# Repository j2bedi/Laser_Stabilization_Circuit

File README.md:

# Laser stabilization circuit repo 

Kicad 9.0 project files located in repo 

production files(gerber and drill) located within releases

Kindly use kicad 9.0 :-)

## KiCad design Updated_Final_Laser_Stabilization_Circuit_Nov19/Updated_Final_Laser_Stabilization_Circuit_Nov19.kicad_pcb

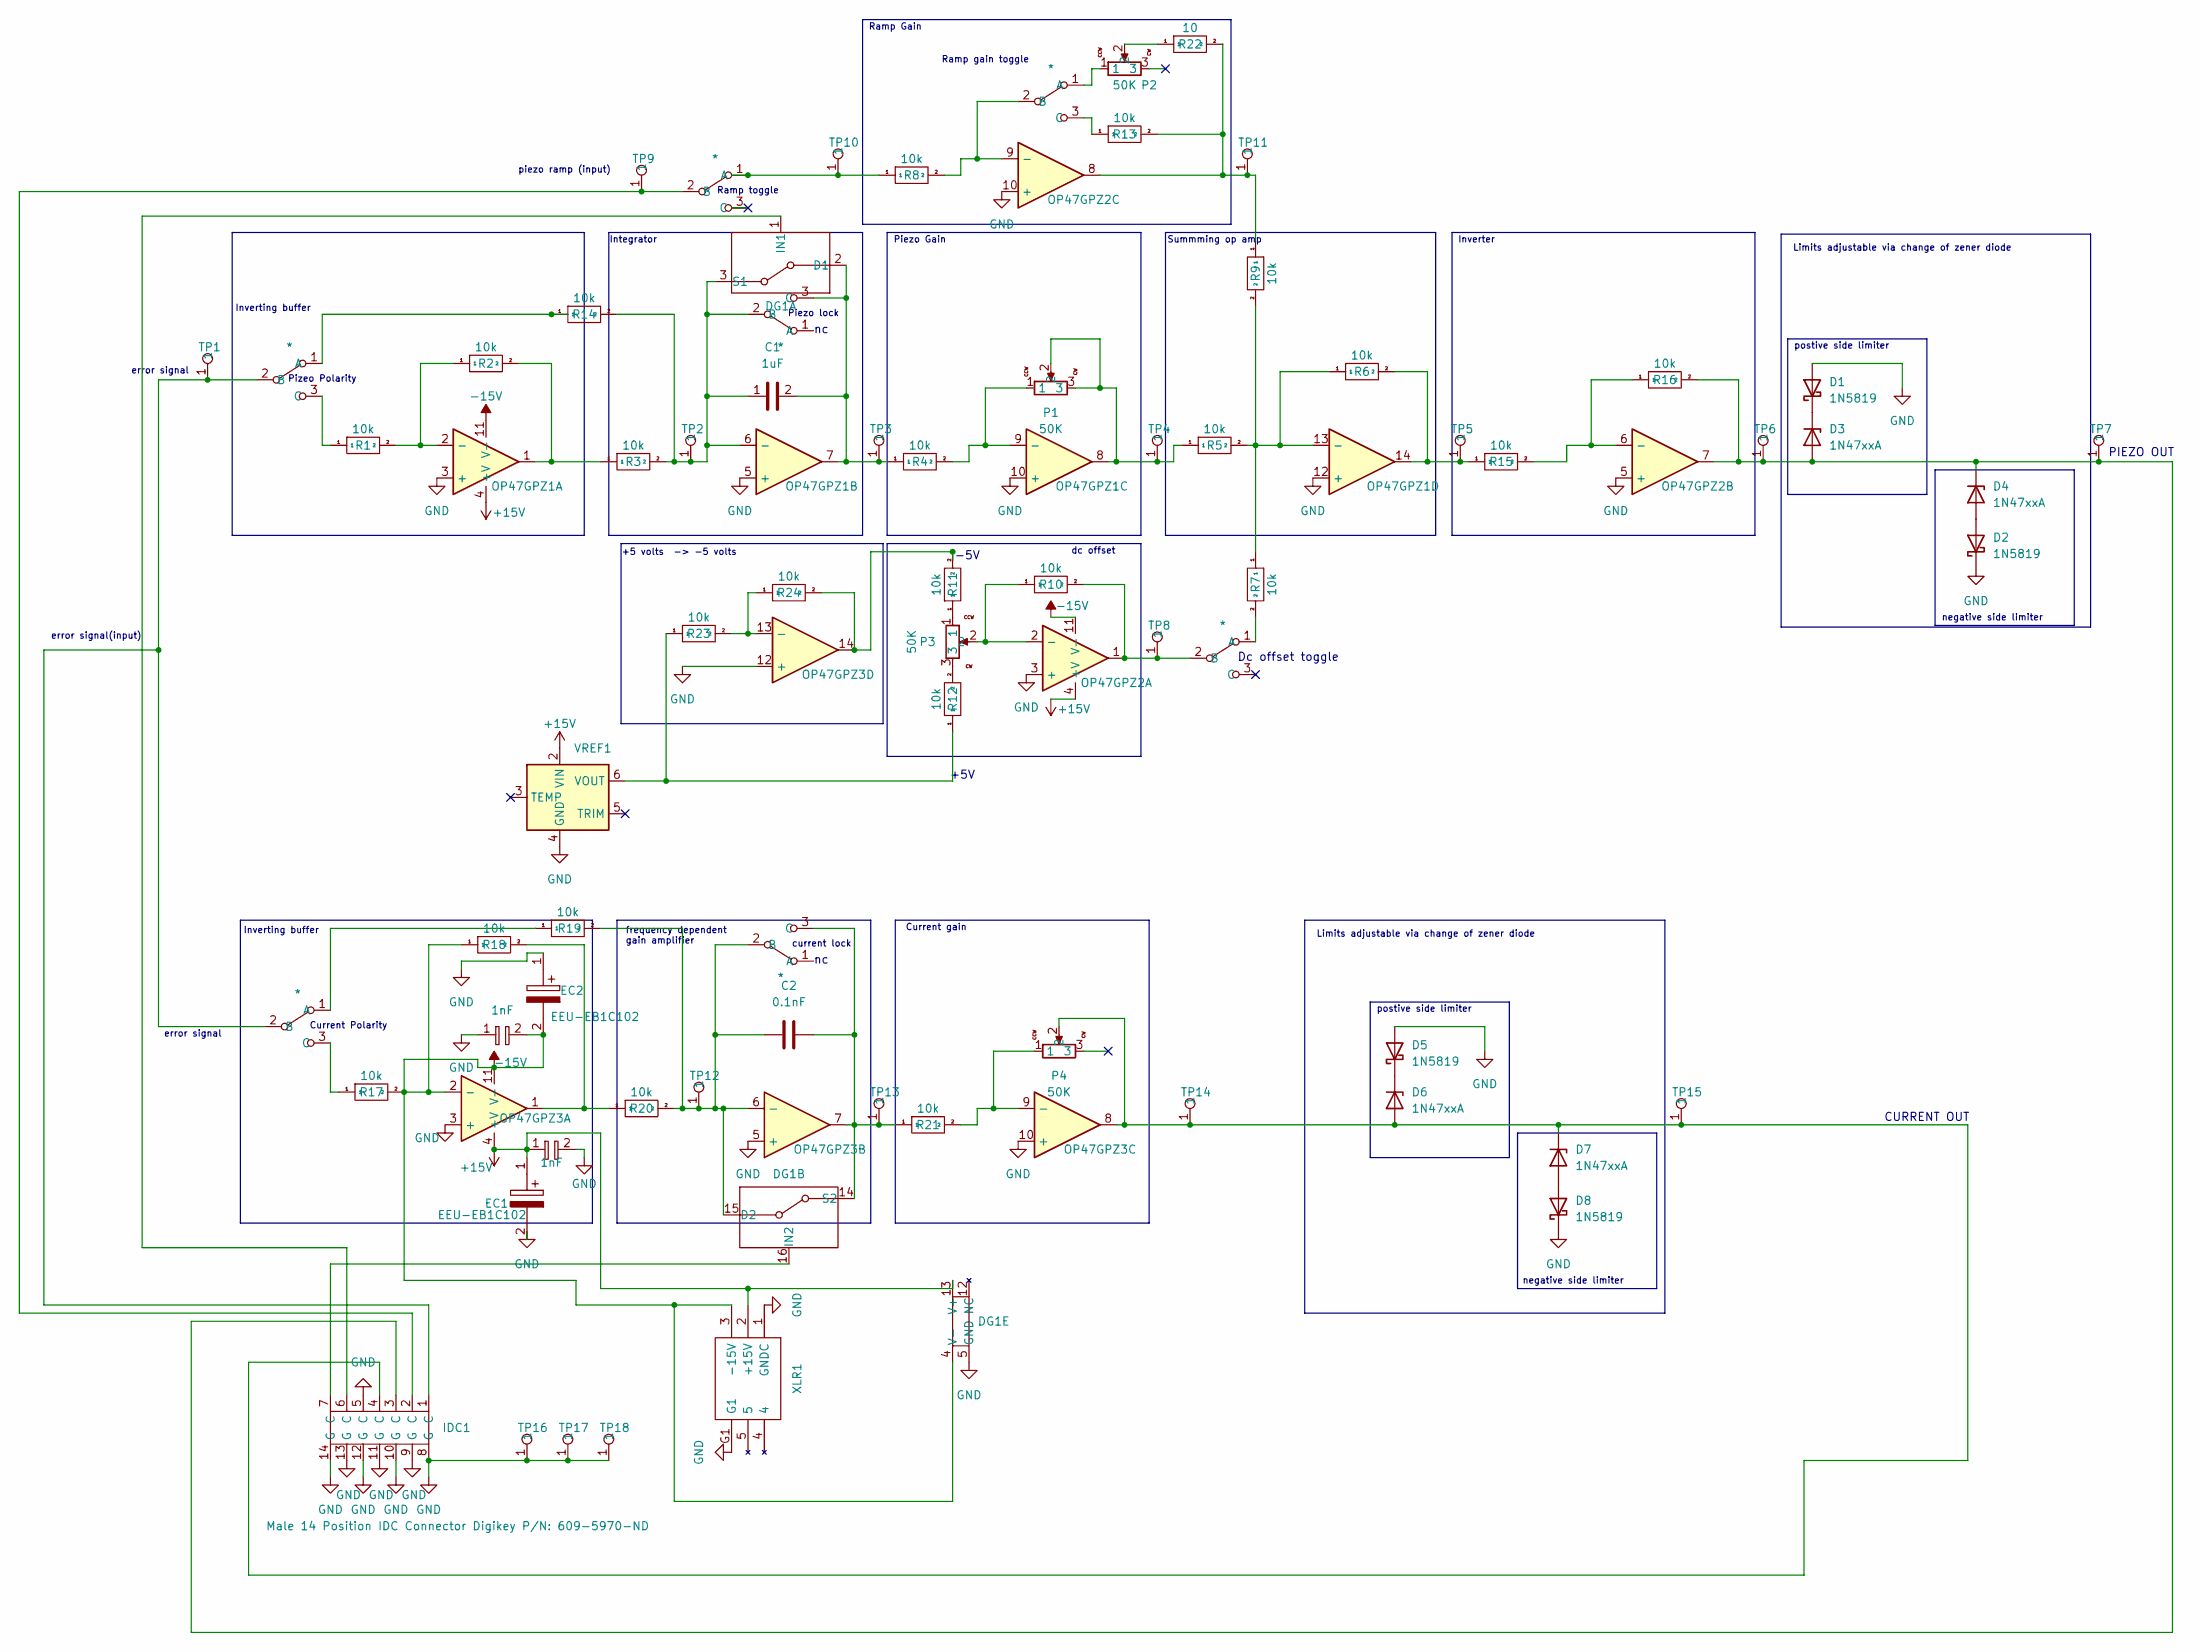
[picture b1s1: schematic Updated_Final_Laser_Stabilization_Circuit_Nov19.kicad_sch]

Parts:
C1: 1uF; CAPACITOR - 399-4209-ND
C2: 0.1nF; CAPACITOR - 399-4209-ND
D1, D2, D5, D8: 1N5819; D_DO-41_SOD81_P10.16mm_Horizontal
D3, D4, D6, D7: 1N47xxA; D_DO-41_SOD81_P10.16mm_Horizontal
DG1: P/N: ADG201AKNZ; Quad Digital Switch ADG201AKNZ; Mouser Part Number 781-DG201HSDY-T1-E3
EC1, EC2: EEU-EB1C102; ELECTROLYTIC CAPACITOR - EEU-EB1C102
IDC1: Male 14 Position IDC Connector Digikey P/N: 609-5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; Male IDC Connector
OP47GPZ1, OP47GPZ2, OP47GPZ3: OP470GPZ Amplifier
P1, P2, P3, P4: 50K; Potentiometer
R1, R2, R3, R4, R5, R6, R7, R8, R9, R10, R11, R12, R13, R14, R15, R16, R17, R18, R19, R20, R21, R23, R24: 10k; R_Axial_DIN0207_L6.3mm_D2.5mm_P10.16mm_Horizontal
R22: 10; R_Axial_DIN0207_L6.3mm_D2.5mm_P10.16mm_Horizontal
SC1, SC2: 1nF; Small Capacitor
SW1, SW2, SW3, SW4, SW5, SW6, SW7: SPDT Switch, P/N: 7101SD9AV2BE; AV2_Switch
TP1, TP2, TP3, TP4, TP5, TP6, TP7, TP8, TP9, TP10, TP11, TP12, TP13, TP14, TP15, TP16, TP17, TP18: TestPoint
VREF1: REF02 P/N: REF02CPZ; REF02CPZ
XLR1: XLR P/N: NC3MBH; NC3MBH_XLR

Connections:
+15V: DG1.13 (V+), EC1.1, OP47GPZ1.4 (+V), OP47GPZ2.4 (+V), OP47GPZ3.4 (+V), SC1.1, VREF1.2 (VIN), XLR1.2 (+15V)
-15V: DG1.4 (V-), EC2.2, OP47GPZ1.11 (V-), OP47GPZ2.11 (V-), OP47GPZ3.2 (-), OP47GPZ3.11 (V-), R17.2, R18.1, SC2.2, XLR1.3 (-15V)
GND: D1.2 (A), D2.1 (K), D5.2 (A), D8.1 (K), DG1.5 (GND), EC1.2, EC2.1, IDC1.5 (C), IDC1.8 (G), IDC1.9 (G), IDC1.10 (G), IDC1.11 (G), IDC1.12 (G), IDC1.13 (G), IDC1.14 (G), OP47GPZ1.3 (+), OP47GPZ1.5 (+), OP47GPZ1.10 (+), OP47GPZ1.12 (+), OP47GPZ2.3 (+), OP47GPZ2.5 (+), OP47GPZ2.10 (+), OP47GPZ3.3 (+), OP47GPZ3.5 (+), OP47GPZ3.10 (+), OP47GPZ3.12 (+), SC1.2, SC2.1, TP16.1, TP17.1, TP18.1, VREF1.4 (GND), XLR1.1 (GNDC), XLR1.G1
unnamed: D1.1 (K), D3.1 (K)
unnamed: D2.2 (A), D4.2 (A)
unnamed: D3.2 (A), D4.1 (K), IDC1.3 (C), OP47GPZ2.7, R16.2, TP6.1, TP7.1
unnamed: D5.1 (K), D6.1 (K)
unnamed: D6.2 (A), D7.1 (K), IDC1.4 (C), OP47GPZ3.8, P4.2, TP14.1, TP15.1
unnamed: D7.2 (A), D8.2 (A)
unnamed: C1.2, DG1.2 (D1), OP47GPZ1.7, R4.1, SW2.3 (C), TP3.1
unnamed: DG1.1 (IN1), IDC1.6 (C)
unnamed: C1.1, DG1.3 (S1), OP47GPZ1.6 (-), R3.2, R14.2, SW2.2 (B), TP2.1
unnamed: C2.1, DG1.15 (D2), OP47GPZ3.6 (-), R19.2, R20.2, SW7.2 (B), TP12.1
unnamed: DG1.16 (IN2), IDC1.7 (C)
unnamed: C2.2, DG1.14 (S2), OP47GPZ3.7, R21.1, SW7.3 (C), TP13.1
unnamed: OP47GPZ1.1, R2.2, R3.1
unnamed: OP47GPZ1.8, P1.2, P1.3, R5.1, TP4.1
unnamed: OP47GPZ1.14, R6.2, R15.1, TP5.1
unnamed: OP47GPZ1.2 (-), R1.2, R2.1
unnamed: OP47GPZ1.9 (-), P1.1, R4.2
unnamed: OP47GPZ1.13 (-), R5.2, R6.1, R7.1, R9.2
unnamed: OP47GPZ2.8, R9.1, R13.2, R22.2, TP11.1
unnamed: OP47GPZ2.2 (-), P3.2, R10.1
unnamed: OP47GPZ2.6 (-), R15.2, R16.1
unnamed: OP47GPZ2.9 (-), R8.2, SW6.2 (B)
unnamed: OP47GPZ3.1, R18.2, R20.1
unnamed: OP47GPZ3.14, R11.2, R24.2
unnamed: OP47GPZ3.9 (-), P4.1, R21.2
unnamed: OP47GPZ3.13 (-), R23.2, R24.1
unnamed: P2.2, R22.1
unnamed: P3.1, R11.1
unnamed: P3.3, R12.2
unnamed: R14.1, SW1.1 (A)
unnamed: IDC1.1 (C), SW1.2 (B), SW3.2 (B), TP1.1
unnamed: R1.1, SW1.3 (C)
unnamed: R19.1, SW3.1 (A)
unnamed: R17.1, SW3.3 (C)
unnamed: R8.1, SW4.1 (A), TP10.1
unnamed: IDC1.2 (C), SW4.2 (B), TP9.1
unnamed: R7.2, SW5.1 (A)
unnamed: OP47GPZ2.1, R10.2, SW5.2 (B), TP8.1
unnamed: P2.1, SW6.1 (A)
unnamed: R13.1, SW6.3 (C)
unnamed: R12.1, R23.1, VREF1.6 (VOUT)

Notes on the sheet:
Inverting buffer
Integrator
+5 volts -> -5 volts
dc offset
error signal
+5V
CURRENT OUT
Piezo Gain
Limits adjustable via change of zener diode
Ramp toggle
postive side limiter
Dc offset toggle
negative side limiter
Inverter
-5V
Piezo lock
current lock
Ramp gain toggle
piezo ramp (input)
Summming op amp
error signal(input)
Ramp Gain
Pizeo Polarity
Current Polarity
frequency dependent gain amplifier
Current gain
PIEZO OUT

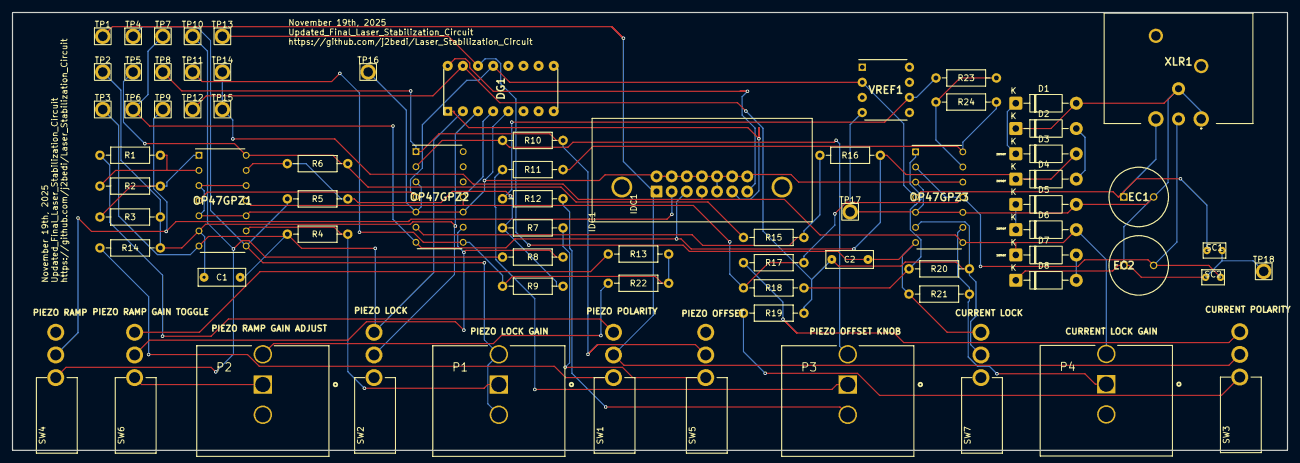
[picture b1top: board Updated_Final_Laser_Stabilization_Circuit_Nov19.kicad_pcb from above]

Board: 2 copper layers, 214.3 x 73.6 mm, 74 parts (0 on the bottom side), 44 nets.

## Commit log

2024-09-28 README.md
2025-10-28 Add files via upload
    test upload - update the board with the text refering to date of production and where to fin d
2025-10-28 updated readme after discussion with jim
    A more organized layout
2025-10-28 Delete FINAL_Laser_Stabilization_Circuit directory
    updated with text indicating reference infomation(date and github repo link)
2025-10-28 Laser stabilization project files
    Contains the project files(if your looking for the production files -> visit the releases page of this repo please)
2025-11-19 Updated addition of LASER PCB files
    Updated the KiCad Project files for the laser stabilization circuit on Nov 19th.
    Adjustments include changes to the positioning of select components on board, addition of the digital switch, and slight modification to some footprints/footprint libraries.
